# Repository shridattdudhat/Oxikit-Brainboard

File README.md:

# Oxikit-Brainboard

An Open Source Oxygen Concentrator Brain Board

Following are details of each directory:

- **BOM** : Bill Of Material for BrainBoard
- **Firmware** : Firmware to use with BrainBoard. It has two different firmware folder. 
  - Particle Electron Firmware
  - ESP32 TTGO T-Call firmware
- **gerberFiles** : You can download the zip and give for production.
- **images** : It has all the 3D images of BrainBoard
- **kicadProject** : It cotains all the files of Kicad Project. One can install latest Kicad nightly build and run the project to modify it. 
- **schematic** : Schematic file of the PCB

Some Kicad generated 3D images:

First prototypes of BrainBoard:

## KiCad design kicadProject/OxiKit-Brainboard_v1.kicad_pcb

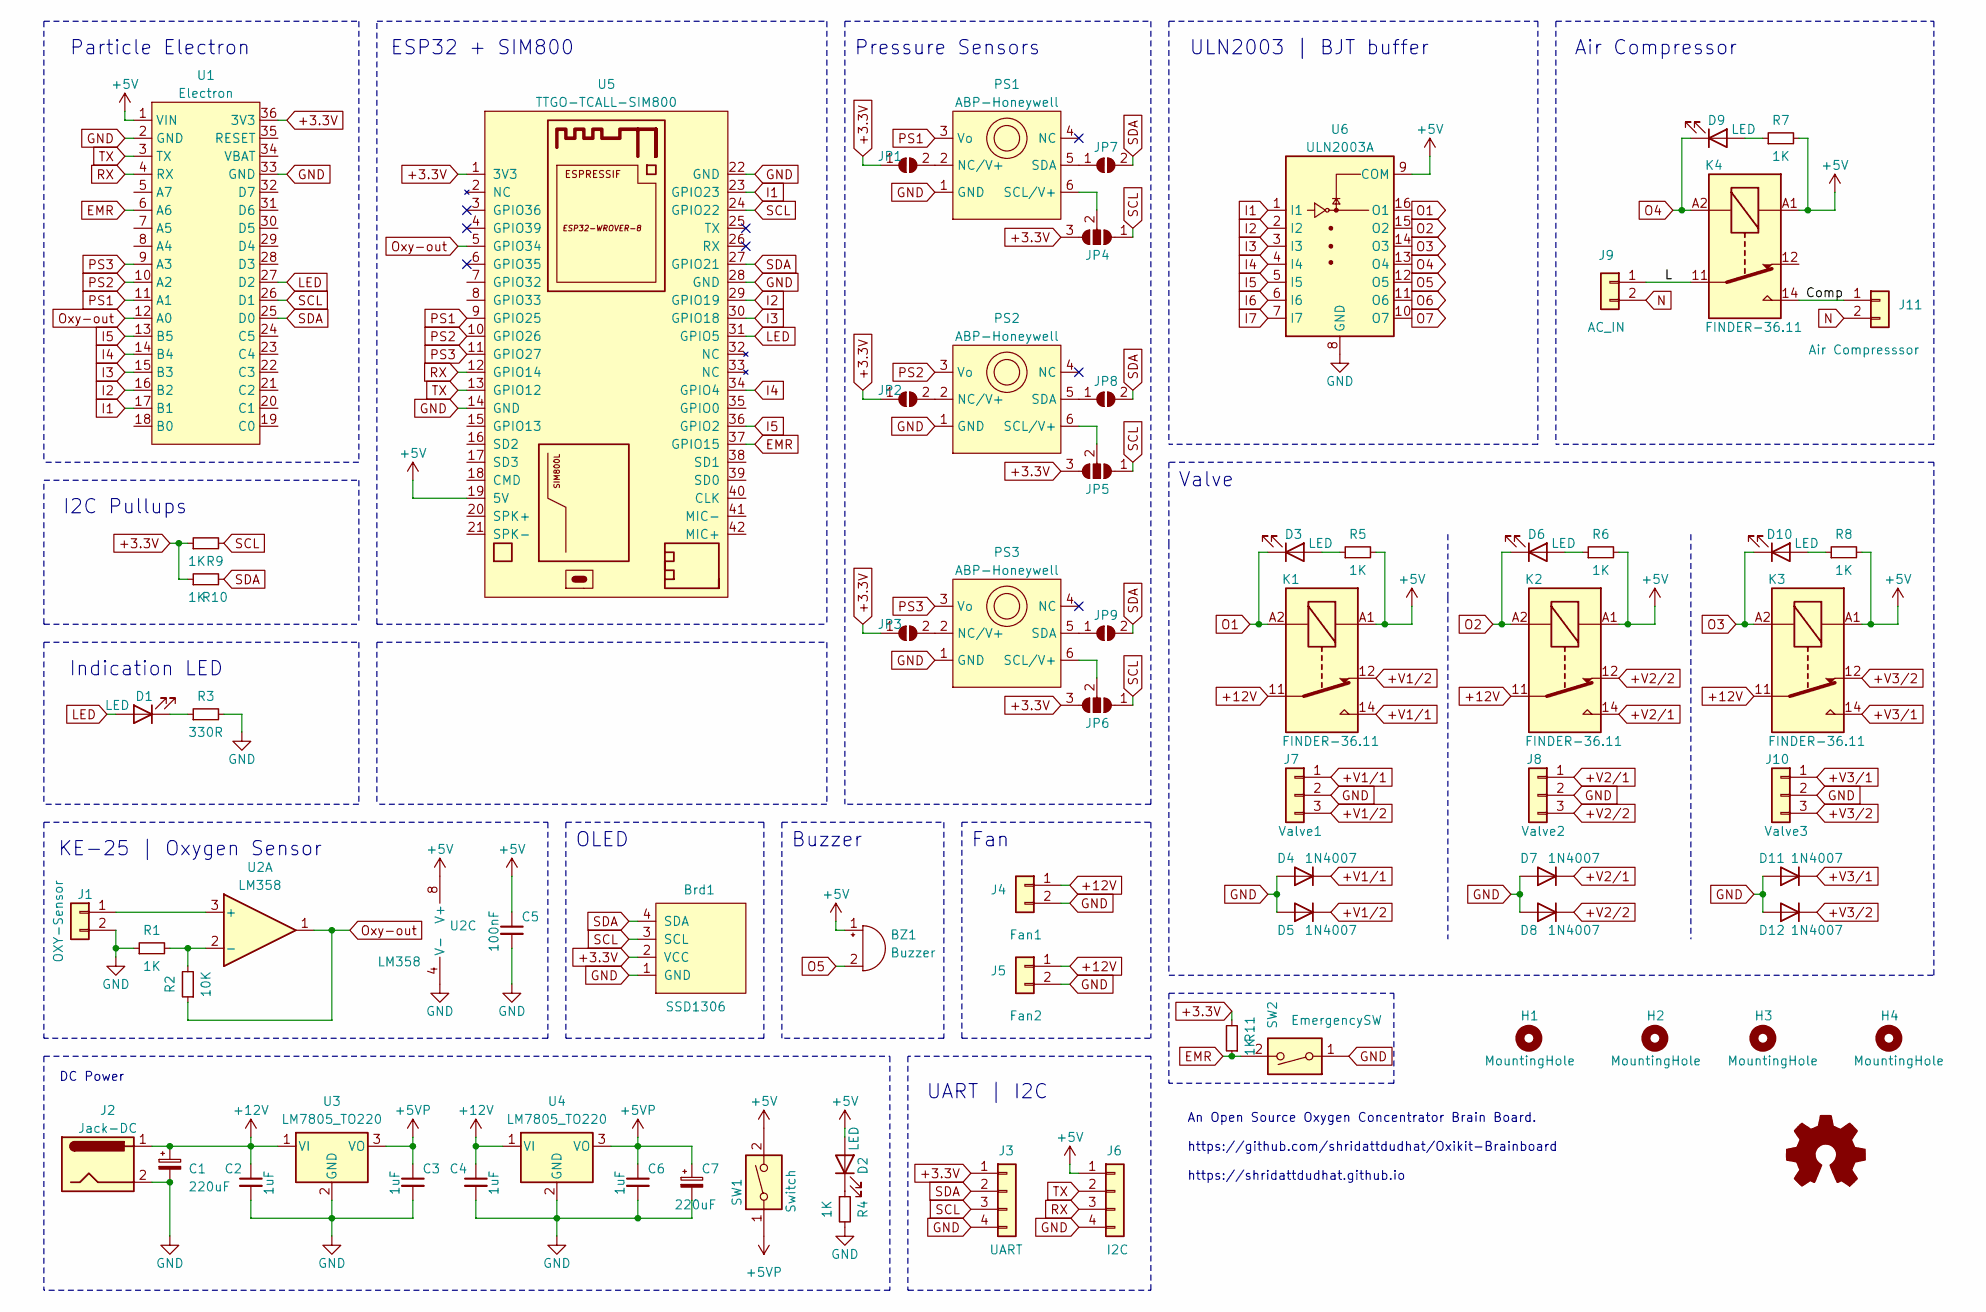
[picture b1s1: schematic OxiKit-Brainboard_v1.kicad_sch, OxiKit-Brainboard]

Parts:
BZ1: Buzzer; Buzzer_12x9.5RM7.6
Brd1: SSD1306; 128x64OLED
C1, C7: 220uF; CP_Radial_D8.0mm_P3.50mm
C2, C3, C4, C6: 1uF; C_0805_2012Metric_Pad1.18x1.45mm_HandSolder
C5: 100nF; C_0805_2012Metric_Pad1.18x1.45mm_HandSolder
D1, D2, D3, D6, D9, D10: LED; LED_1206_3216Metric_Pad1.42x1.75mm_HandSolder
D4, D5, D7, D8, D11, D12: 1N4007; D_DO-41_SOD81_P10.16mm_Horizontal
H1, H2, H3, H4: MountingHole; MountingHole_3.2mm_M3_Pad_Via
J1: OXY-Sensor; JST_XH_B2B-XH-A_1x02_P2.50mm_Vertical
J2: Jack-DC; BarrelJack_Wuerth_6941xx301002
J3: UART; JST_XH_B4B-XH-A_1x04_P2.50mm_Vertical
J4: Fan1; TerminalBlock_bornier-2_P5.08mm
J5: Fan2; TerminalBlock_bornier-2_P5.08mm
J6: I2C; JST_XH_B4B-XH-A_1x04_P2.50mm_Vertical
J7: Valve1; TerminalBlock_bornier-3_P5.08mm
J8: Valve2; TerminalBlock_bornier-3_P5.08mm
J9: AC_IN; TerminalBlock_bornier-2_P5.08mm
J10: Valve3; TerminalBlock_bornier-3_P5.08mm
J11: Air Compresssor; TerminalBlock_bornier-2_P5.08mm
JP1, JP2, JP3, JP7, JP8, JP9: SolderJumper_2_Open; SolderJumper-2_P1.3mm_Open_RoundedPad1.0x1.5mm
JP4, JP5, JP6: SolderJumper_3_Open; SolderJumper-3_P1.3mm_Open_RoundedPad1.0x1.5mm_NumberLabels
K1, K2, K3, K4: FINDER-36.11; Relay_SPDT_Finder_36.11
PS1, PS2, PS3: ABP-Honeywell; ABP-Series-Pressure
R1, R4, R5, R6, R7, R8, R9, R10, R11: 1K; R_0805_2012Metric_Pad1.20x1.40mm_HandSolder
R2: 10K; R_0805_2012Metric_Pad1.20x1.40mm_HandSolder
R3: 330R; R_0805_2012Metric_Pad1.20x1.40mm_HandSolder
SW1: Switch; JST_XH_B2B-XH-A_1x02_P2.50mm_Vertical
SW2: EmergencySW; JST_XH_B2B-XH-A_1x02_P2.50mm_Vertical
U1: Electron; electron
U2: LM358
U3, U4: LM7805_TO220; TO-220-3_Vertical
U5: TTGO-TCALL-SIM800
U6: ULN2003A; DIP-16_W7.62mm_LongPads

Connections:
+3.3V: Brd1.2 (VCC), J3.1, JP1.1 (A), JP2.1 (A), JP3.1 (A), JP4.3 (B), JP5.3 (B), JP6.3 (B), R9.1, R10.1, R11.2, U1.36 (3V3), U5.1 (3V3)
+5V: BZ1.1 (-), C5.1, D2.2 (A), J6.1, K1.A1, K2.A1, K3.A1, K4.A1, R5.2, R6.2, R7.2, R8.2, SW1.2, U1.1 (VIN), U2.8 (V+), U5.19 (5V), U6.9 (COM)
+5VP: C3.1, C6.1, C7.1, SW1.1, U3.3 (VO), U4.3 (VO)
+12V: C1.1, C2.1, C4.1, J2.1, J4.1, J5.1, K1.11, K2.11, K3.11, U3.1 (VI), U4.1 (VI)
+V1/1: D4.1 (K), J7.1, K1.14
+V1/2: D5.1 (K), J7.3, K1.12
+V2/1: D7.1 (K), J8.1, K2.14
+V2/2: D8.1 (K), J8.3, K2.12
+V3/1: D11.1 (K), J10.1, K3.14
+V3/2: D12.1 (K), J10.3, K3.12
/Comp: J11.1, K4.14
/L: J9.1, K4.11
EMR: R11.1, SW2.2, U1.6 (A6), U5.37 (GPIO15)
GND: Brd1.1 (GND), C1.2, C2.2, C3.2, C4.2, C5.2, C6.2, C7.2, D4.2 (A), D5.2 (A), D7.2 (A), D8.2 (A), D11.2 (A), D12.2 (A), J1.2, J2.2, J3.4, J4.2, J5.2, J6.4, J7.2, J8.2, J10.2, PS1.1 (GND), PS2.1 (GND), PS3.1 (GND), R1.1, R3.2, R4.2, SW2.1, U1.2 (GND), U1.33 (GND), U2.4 (V-), U3.2 (GND), U4.2 (GND), U5.14 (GND), U5.22 (GND), U5.28 (GND), U6.8 (GND)
I1: U1.17 (B1), U5.23 (GPIO23), U6.1 (I1)
I2: U1.16 (B2), U5.29 (GPIO19), U6.2 (I2)
I3: U1.15 (B3), U5.30 (GPIO18), U6.3 (I3)
I4: U1.14 (B4), U5.34 (GPIO4), U6.4 (I4)
I5: U1.13 (B5), U5.36 (GPIO2), U6.5 (I5)
I6: U6.6 (I6)
I7: U6.7 (I7)
LED: D1.2 (A), U1.27 (D2), U5.31 (GPIO5)
N: J9.2, J11.2
unnamed: D1.1 (K), R3.1
unnamed: D2.1 (K), R4.1
unnamed: D3.2 (A), R5.1
unnamed: D6.2 (A), R6.1
unnamed: D9.2 (A), R7.1
unnamed: D10.2 (A), R8.1
unnamed: J1.1, U2.3 (+)
unnamed: JP1.2 (B), PS1.2 (NC/V+)
unnamed: JP2.2 (B), PS2.2 (NC/V+)
unnamed: JP3.2 (B), PS3.2 (NC/V+)
unnamed: JP4.2 (C), PS1.6 (SCL/V+)
unnamed: JP5.2 (C), PS2.6 (SCL/V+)
unnamed: JP6.2 (C), PS3.6 (SCL/V+)
unnamed: JP7.1 (A), PS1.5 (SDA)
unnamed: JP8.1 (A), PS2.5 (SDA)
unnamed: JP9.1 (A), PS3.5 (SDA)
unnamed: R1.2, R2.2, U2.2 (-)
O1: D3.1 (K), K1.A2, U6.16 (O1)
O2: D6.1 (K), K2.A2, U6.15 (O2)
O3: D10.1 (K), K3.A2, U6.14 (O3)
O4: D9.1 (K), K4.A2, U6.13 (O4)
O5: BZ1.2 (+), U6.12 (O5)
O6: U6.11 (O6)
O7: U6.10 (O7)
Oxy-out: R2.1, U1.12 (A0), U2.1, U5.5 (GPIO34)
PS1: PS1.3 (Vo), U1.11 (A1), U5.9 (GPIO25)
PS2: PS2.3 (Vo), U1.10 (A2), U5.10 (GPIO26)
PS3: PS3.3 (Vo), U1.9 (A3), U5.11 (GPIO27)
RX: J6.3, U1.4 (RX), U5.12 (GPIO14)
SCL: Brd1.3 (SCL), J3.3, JP4.1 (A), JP5.1 (A), JP6.1 (A), R9.2, U1.26 (D1), U5.24 (GPIO22)
SDA: Brd1.4 (SDA), J3.2, JP7.2 (B), JP8.2 (B), JP9.2 (B), R10.2, U1.25 (D0), U5.27 (GPIO21)
TX: J6.2, U1.3 (TX), U5.13 (GPIO12)

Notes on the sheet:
DC Power
I2C Pullups
Indication LED
Particle Electron
KE-25 | Oxygen Sensor
ESP32 + SIM800
OLED
Buzzer
Pressure Sensors
UART | I2C
Fan
Valve
An Open Source Oxygen Concentrator Brain Board. https://github.com/shridattdudhat/Oxikit-Brainboard https://shridattdudhat.github.io
ULN2003 | BJT buffer
Air Compressor

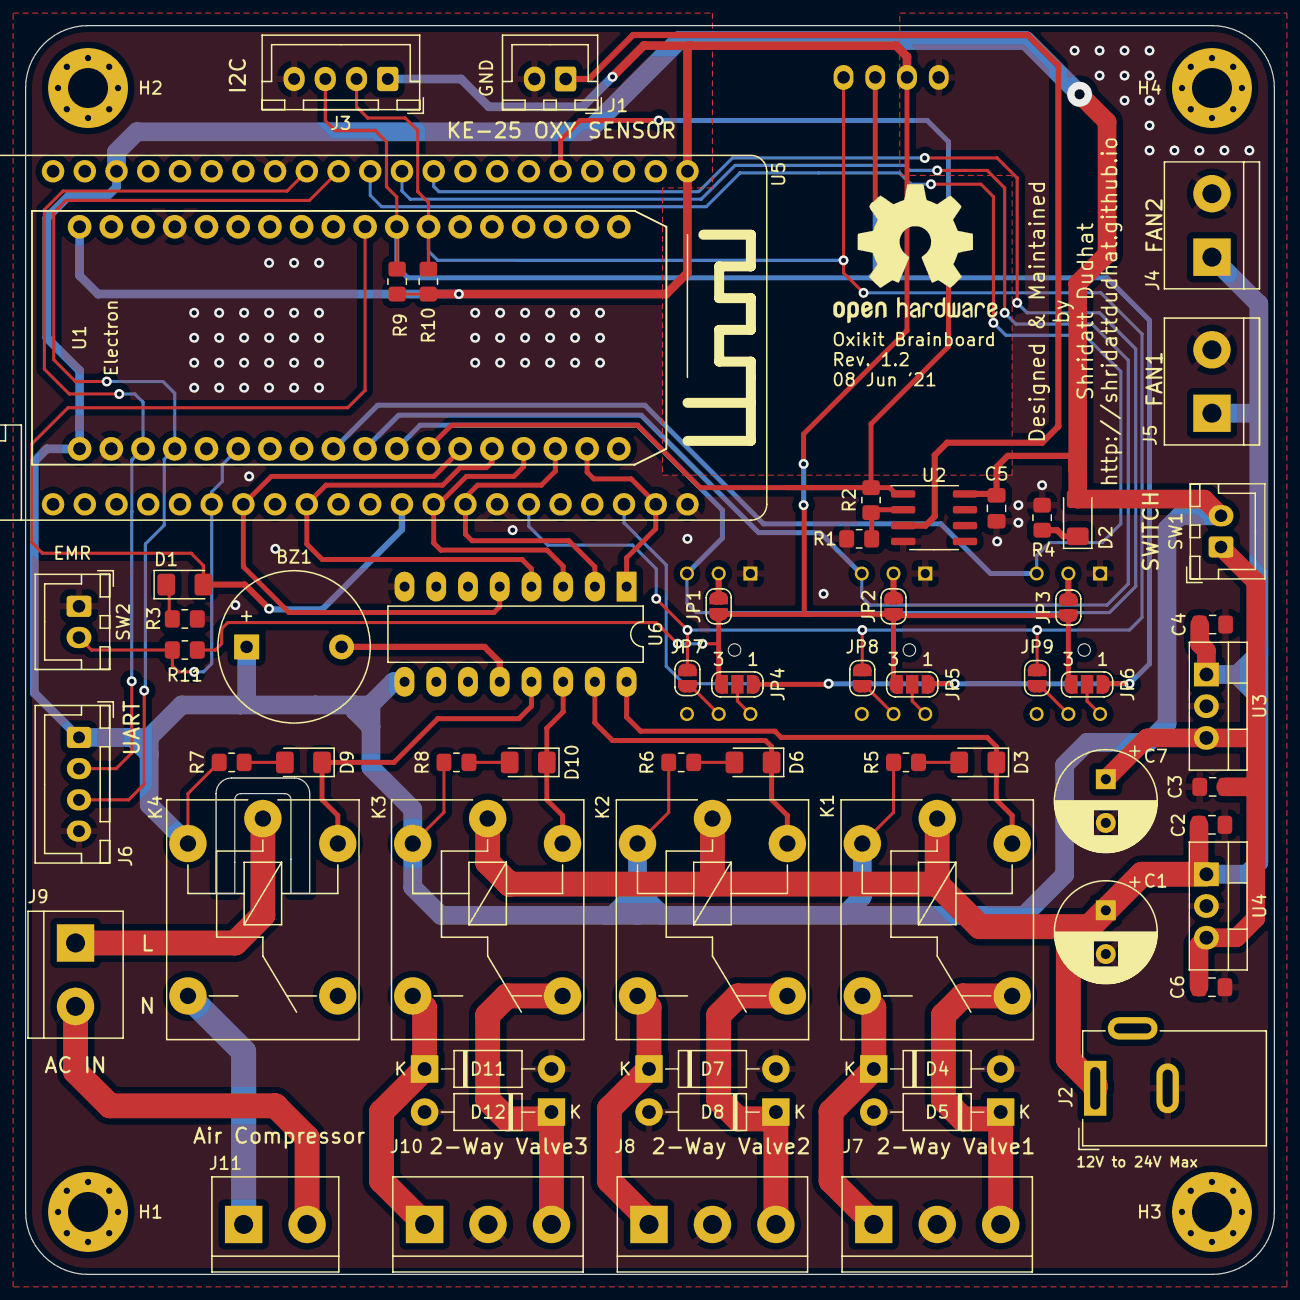
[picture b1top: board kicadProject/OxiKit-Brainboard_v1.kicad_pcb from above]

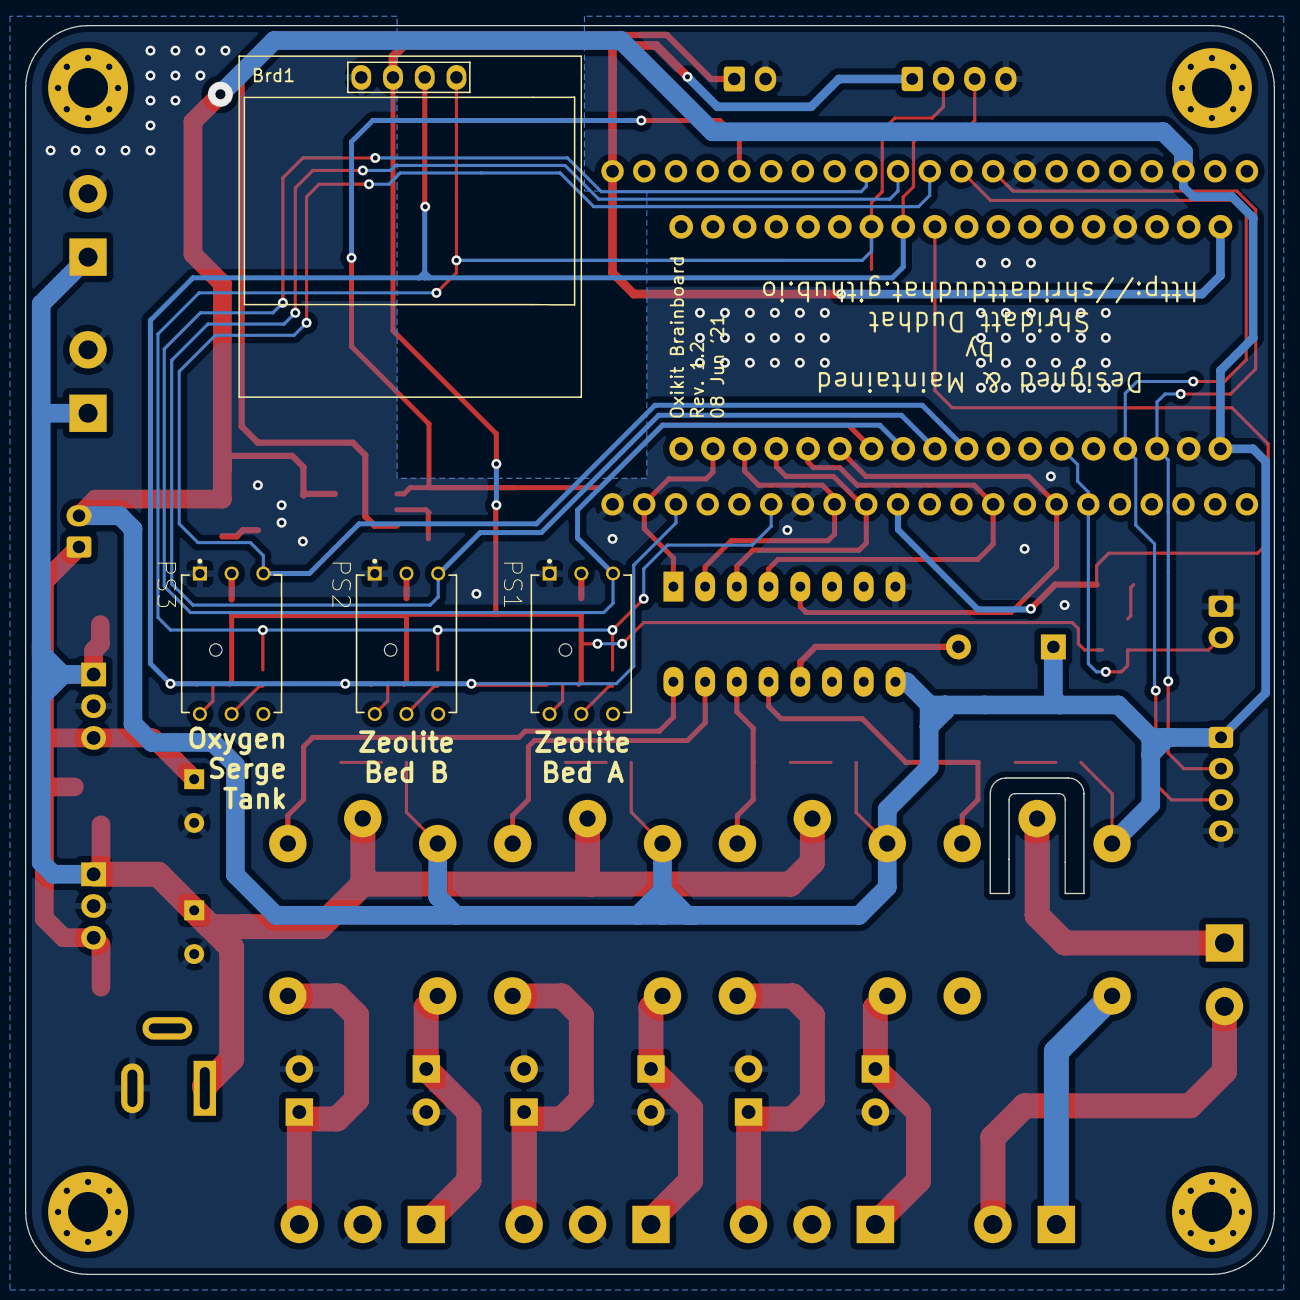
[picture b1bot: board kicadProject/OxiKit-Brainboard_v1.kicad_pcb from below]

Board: 2 copper layers, 100.0 x 100.0 mm, 71 parts (4 on the bottom side), 51 nets.

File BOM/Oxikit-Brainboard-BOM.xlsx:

Sr. No. | Designator | Component value | Manufacturer Part Number | Qty per PCB | Package / Case | Per Component | Per PCB | Description | Ref Link (Local Purchase)
1 | Brd1 | SSD1306 | * | 1 | SSD1306:128x64OLED | 300 | 300 | I2C OLED Display | https://www.sunrobotics.in/shop/product/7375-oled-0-96-inch-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
2 | BZ1 | Buzzer | * | 1 | Buzzer_Beeper:Buzzer_12x9.5RM7.6 | 15 | 15 | Electromagnetic Active Buzzer 5V | https://www.sunrom.com/p/electromagnetic-active-buzzer-5v
3 | C1, C7 | 220uF | MCGPR16V227M6.3X11 | 2 | Capacitor_THT:CP_Radial_D8.0mm_P3.50mm | 3 | 6 | Electrolytic Capacitor, 220 µF, 16 V, MCGPR Series, ± 20%, Radial Leaded, 2000 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
4 | C2, C3, C4, C6 | 1uF | MC0805F105Z500CT | 4 | Capacitor_SMD:C_0805_2012Metric_Pad1.18x1.45mm_HandSolder | 2 | 8 | 1 µF, 50 V, 0805 [2012 Metric] | https://www.sunrom.com/p/1uf-105-0805-2012-metric
5 | C5 | 100nF | MC0805B104M500CT | 1 | Capacitor_SMD:C_0805_2012Metric_Pad1.18x1.45mm_HandSolder | 1 | 1 | 0.1 µF, 50 V, 0805 [2012 Metric], ± 20%, X7R | https://www.sunrom.com/p/100nf-104-0805-2012-metric
6 | D1, D2, D3, D6, D9, D10 | LED | * | 6 | LED_SMD:LED_1206_3216Metric_Pad1.42x1.75mm_HandSolder | 1 | 6 | Red SMD LED 1206 | https://www.sunrom.com/p/red-smd-led-1206
7 | D4, D5, D7, D8, D11, D12 | 1N4007 | 1N4007 | 6 | Diode_THT:D_DO-41_SOD81_P10.16mm_Horizontal | 1.5 | 9 | DIODE, STANDARD RECOVERY, 1A, 1KV, DO-41 | https://www.sunrom.com/p/1n4007-1a-diode
8 | J1 | OXY-Sensor | * | 1 | Connector_JST:JST_XH_B2B-XH-A_1x02_P2.50mm_Vertical | 1.5 | 1.5 | JST 2 Pin 2.54mm Pitch | https://www.sunrom.com/p/2-pin-jst-xh-25mm-top-entry-header
9 | J2 | Jack-DC | * | 1 | Connector_BarrelJack:BarrelJack_Wuerth_6941xx301002 | 13 | 13 | DC Socket - 1mm legs - Suitable for 5.5x2.1mm DC Pins | https://www.sunrom.com/p/dc-socket---1mm-legs---suitable-for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
10 | J3, J6 | UART, I2C | * | 2 | Connector_JST:JST_XH_B4B-XH-A_1x04_P2.50mm_Vertical |  |  | 4 pin JST XH 2.5mm Top Entry Header | https://www.sunrom.com/p/4-pin-jst-xh-25mm-top-entry-header
11 | J4, J5, J9, J11 | Fan1 | * | 4 | TerminalBlock:TerminalBlock_bornier-2_P5.08mm | 7 | 28 | 2P 5mm 10A Screw Terminal Light | https://www.sunrom.com/p/2p-5mm-10a-screw-terminal-light
12 | J7, J8, J10 | Valve1 | * | 3 | TerminalBlock:TerminalBlock_bornier-3_P5.08mm | 11 | 33 | 3P 5mm 10A Screw Terminal Light | https://www.sunrom.com/p/3p-5mm-10a-screw-terminal-light
13 | K1, K2, K3, K4 | FINDER-36.11 | * | 4 | Relay_THT:Relay_SPDT_Finder_36.11 | 24 | 100 | Relay 5V - PCB Mount | https://www.sunrom.com/p/relay-5v-pcb-mount
14 | R1, R4, R5, R6, R7, R8, R9, R10, R11 | 1K | MCWR08X1001FTL | 9 | Resistor_SMD:R_0805_2012Metric_Pad1.20x1.40mm_HandSolder | 0.5 | 5 | 1 kohm, ± 1%, 125 mW, 0805 [2012 Metric] | https://www.sunrom.com/p/1k-1-0805-pack-of-100
15 | R2 | 10K | MCWR08X1002FTL | 1 | Resistor_SMD:R_0805_2012Metric_Pad1.20x1.40mm_HandSolder | 0.5 | 0.5 | 10 kohm, ± 1%, 125 mW, 0805 [2012 Metric] | https://www.sunrom.com/p/10k-1-0805-pack-of-100
16 | R3 | 330R | MCWR08X3300FTL | 1 | Resistor_SMD:R_0805_2012Metric_Pad1.20x1.40mm_HandSolder | 0.5 | 0.5 | 330 ohm, ± 1%, 125 mW, 0805 [2012 Metric] | https://www.sunrom.com/m/6867
18 | SW1, SW2 | Switch | * | 2 | Connector_JST:JST_XH_B2B-XH-A_1x02_P2.50mm_Vertical |  |  | JST 2 Pin 2.54mm Pitch | https://www.sunrom.com/p/2-pin-jst-xh-25mm-top-entry-header
19 | U1 | Electron |  | 1 | particle:electron
20 | U2 | LM358 | LM358EDR2G | 1 | Package_SO:SOIC-8_3.9x4.9mm_P1.27mm | 13 | 13 | Operational Amplifier, 2 Amplifier, 1 MHz, 0.6 V/µs, 3V to 32V, SOIC, 8 Pins
21 | U3, U4 | LM7805_TO220 | L7805CV | 2 | Package_TO_SOT_THT:TO-220-3_Vertical | 15 | 30 | Linear Voltage Regulator, 7805, Fixed, Positive, 10V To 35V In, 5V And 1.5A Out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
22 | U5 | TTGO-TCALL-SIM800 |  | 1 | TTGO-TCALL-SIM800:TTGO-TCALL-SIM800
23 | U6 | ULN2003A | ULN2003AN . | 1 | Package_DIP:DIP-16_W7.62mm_LongPads | 21 | 21 | Bipolar Transistor Array, NPN, 50 V, 500 mA, 25 W, 600 hFE, DIP | https://www.sunrom.com/p/uln2003a-dip
 |  |  | * Please Check links in last column

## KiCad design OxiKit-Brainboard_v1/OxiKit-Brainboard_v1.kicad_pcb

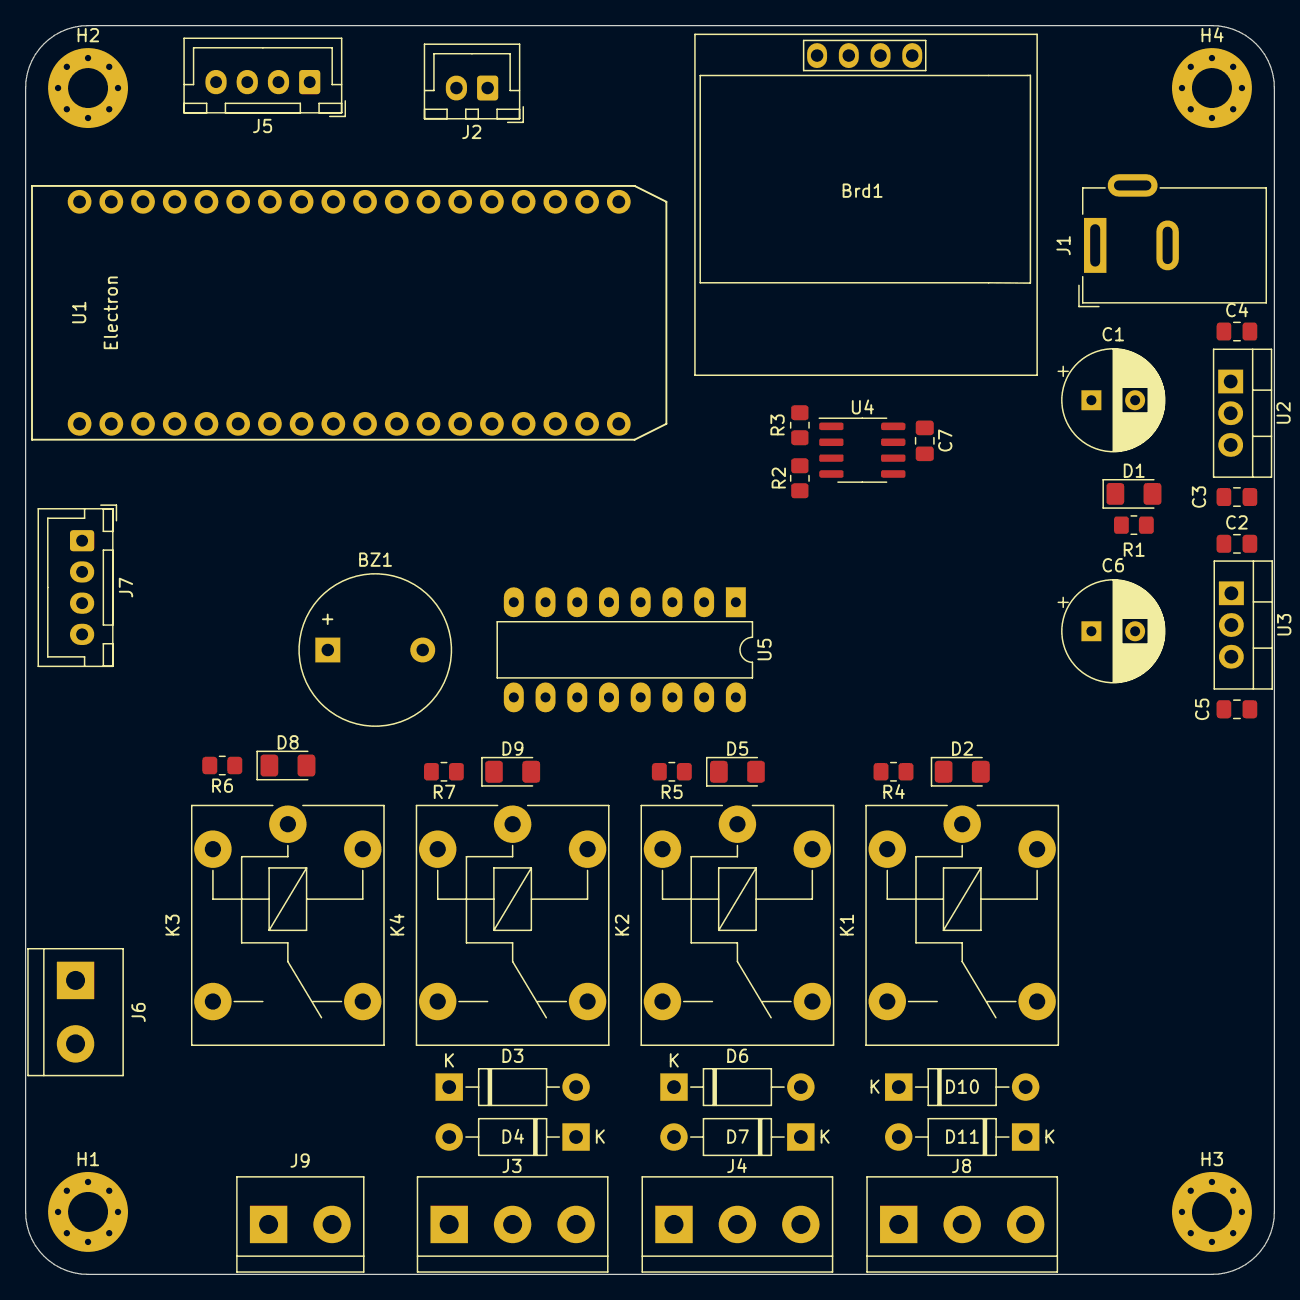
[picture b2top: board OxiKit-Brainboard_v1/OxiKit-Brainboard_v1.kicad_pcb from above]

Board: 2 copper layers, 100.0 x 100.0 mm, 49 parts (0 on the bottom side), 36 nets, no tracks yet.

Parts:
BZ1: Buzzer; Buzzer_12x9.5RM7.6
Brd1: SSD1306; 128x64OLED
C1, C6: 220uF; CP_Radial_D8.0mm_P3.50mm
C2, C3, C4, C5: 1uF; C_0805_2012Metric_Pad1.18x1.45mm_HandSolder
C7: 100nF; C_0805_2012Metric_Pad1.18x1.45mm_HandSolder
D1, D2, D5, D8, D9: LED; LED_1206_3216Metric_Pad1.42x1.75mm_HandSolder
D3, D4, D6, D7, D10, D11: 1N4007; D_DO-41_SOD81_P10.16mm_Horizontal
H1, H2, H3, H4: MountingHole; MountingHole_3.2mm_M3_Pad_Via
J1: Jack-DC; BarrelJack_Wuerth_6941xx301002
J2: OXY-Sensor; JST_XH_B2B-XH-A_1x02_P2.50mm_Vertical
J3: Valve1; TerminalBlock_bornier-3_P5.08mm
J4: Valve2; TerminalBlock_bornier-3_P5.08mm
J5: UART; JST_XH_B4B-XH-A_1x04_P2.50mm_Vertical
J6: AC_IN; TerminalBlock_bornier-2_P5.08mm
J7: I2C; JST_XH_B4B-XH-A_1x04_P2.50mm_Vertical
J8: Valve3; TerminalBlock_bornier-3_P5.08mm
J9: Air Compresssor; TerminalBlock_bornier-2_P5.08mm
K1, K2, K3, K4: FINDER-36.11; Relay_SPDT_Finder_36.11
R1, R2, R4, R5, R6, R7: 1K; R_0805_2012Metric_Pad1.20x1.40mm_HandSolder
R3: 10K; R_0805_2012Metric_Pad1.20x1.40mm_HandSolder
U1: Electron; electron
U2, U3: LM7805_TO220; TO-220-3_Vertical
U4: LM358; SOIC-8_3.9x4.9mm_P1.27mm
U5: ULN2003A; DIP-16_W7.62mm_LongPads

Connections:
+3.3V: Brd1.2 (VCC), J5.1
+5V: BZ1.1 (-), C3.1, C5.1, C6.1, C7.1, D1.2 (A), J7.1, U1.1 (VIN), U2.3 (VO), U3.3 (VO), U4.8 (V+), U5.9 (COM)
+12V: C1.1, C2.1, C4.1, J1.1, K1.11, K2.11, K4.11, U2.1 (VI), U3.1 (VI)
+V1/1: D3.1 (K), J3.1, K1.12
+V1/2: D4.1 (K), J3.3, K1.14
+V2/1: D6.1 (K), J4.1, K2.12
+V2/2: D7.1 (K), J4.3, K2.14
+V3/1: D10.1 (K), J8.1, K4.12
+V3/2: D11.1 (K), J8.3, K4.14
/Comp: J9.1, K3.14
/L: J6.1, K3.11
GND: Brd1.1 (GND), C1.2, C2.2, C3.2, C4.2, C5.2, C6.2, C7.2, D3.2 (A), D4.2 (A), D6.2 (A), D7.2 (A), D10.2 (A), D11.2 (A), J1.2, J2.2, J3.2, J4.2, J5.4, J7.4, J8.2, K1.A1, K2.A1, K3.A1, K4.A1, R1.2, R2.1, R4.2, R5.2, R6.2, R7.2, U1.2 (GND), U1.33 (GND), U2.2 (GND), U3.2 (GND), U4.4 (V-), U5.8 (GND)
I1: U1.18 (B0), U5.1 (I1)
I2: U1.17 (B1), U5.2 (I2)
I3: U1.16 (B2), U5.3 (I3)
I4: U1.15 (B3), U5.4 (I4)
I5: U1.14 (B4), U5.5 (I5)
I6: U1.13 (B5), U5.6 (I6)
N: J6.2, J9.2
unnamed: D1.1 (K), R1.1
unnamed: D2.1 (K), R4.1
unnamed: D5.1 (K), R5.1
unnamed: D8.1 (K), R6.1
unnamed: D9.1 (K), R7.1
unnamed: J2.1, U4.3 (+)
unnamed: R2.2, R3.2, U4.2 (-)
O1: D2.2 (A), K1.A2, U5.16 (O1)
O2: D5.2 (A), K2.A2, U5.15 (O2)
O3: D9.2 (A), K4.A2, U5.14 (O3)
O4: D8.2 (A), K3.A2, U5.13 (O4)
O5: BZ1.2 (+), U5.12 (O5)
Oxy-out: R3.1, U1.12 (A0), U4.1
RX: J7.3, U1.4 (RX)
SCL: Brd1.3 (SCL), J5.3, U1.26 (D1)
SDA: Brd1.4 (SDA), J5.2, U1.25 (D0)
TX: J7.2, U1.3 (TX)

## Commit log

2021-05-18 Initial Schematic Commit | Relays, Buzzer, OxySensor, Power Supply, OLED
2021-05-19 Component Placement - L1
2021-05-19 Final routing
2021-05-19 Updated Folder structure details
2021-05-19 Folder system updated
2021-05-19 Images added
2021-05-19 BOM and Firmware folder added
2021-05-19 Schematic added
2021-05-26 #1 ULN2003 and Relay connection Fixed, Indication LED of Relay also updated
2021-05-26 OSHW Logo Added
2021-05-26 New Gerber Files | #1 Fixed
2021-05-26 Schematic Updated
2021-05-29 ABP Honeywell Pressure Sensor added
2021-05-29 New Gerber added with DIP Pressure Sensor
2021-05-29 New Image Renders
2021-06-08 Pressure Sensor connection to ESP32 #2
    PS1 >> IO25
    PS2 >> IO26
    PS3 >> IO27
2022-12-30 clean
